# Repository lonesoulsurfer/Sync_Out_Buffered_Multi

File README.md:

Buffered Multiple for Modular Synths - Powered by Arduino

Vid of the Sync in action
https://youtu.be/81T7WBMwU_8

Step by step guide (Instructables)
https://www.instructables.com/Buffered-Multiple-for-Modular-Synths-Powered-by-Ar/

Takes one sync input signal and produces six individually configurable outputs
 - Shows current BPM on OLED display
 - Each output can be configured with:
      - Normal sync (1:1)
      - Clock division (1/2, 1/4, 1/8)
      - Three groove patterns:
          - GS: Swing (delays off-beats by fixed amount)
          - GF: Shuffle (creates triplet-based rhythm)
          - GH: Humanize (adds random timing variations)

Groove Implementation 

Swing (GS) = consistent delayed off-beats
 -Delays off-beats by shifting timing up to 66% through beat
- Very classic swing feel at 50-75% intensities
- Clean implementation with consistent timing

Shuffle (GF) = polyrhythmic feel with specific timing ratios
- Creates 2-against-3 feel using weighted offset timing
- Distinct from swing - pushes toward triplet territory
- At 75%, approaches dotted 8th feeling (funkier)

Humanize (GH) = unpredictable variations
- Adds random timing variation around off-beats
- Much stronger randomization (up to 40% of beat)
- More chaotic/organic feel compared to others

The implementation provides good sonic variety between the modes. Each mode serves a distinct musical purpose, and the intensity levels (50%/75%) allow meaningful adjustment.
The two intensity levels (50% and 75%) offer enough adjustability without overcomplicating the interface. This gives users six distinct groove feels to choose from (three types × two intensities), which is a good balance for this type of device.

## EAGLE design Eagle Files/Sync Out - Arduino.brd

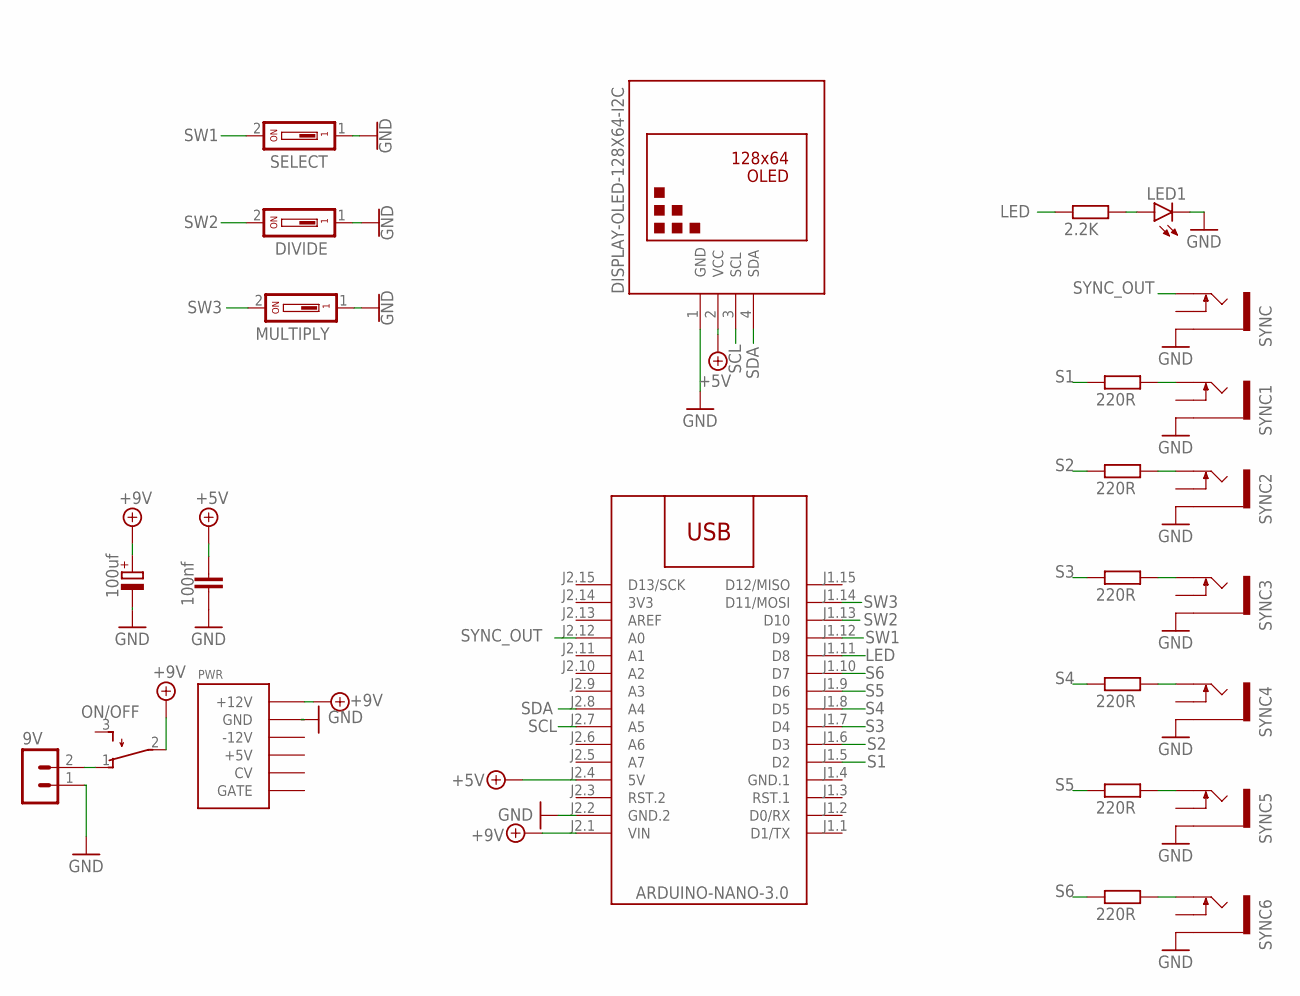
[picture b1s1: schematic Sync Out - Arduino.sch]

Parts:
9V: B2B-PH-K-S
C1: 100nf; C050-024X044
C3: 100uf; E2-5
DIVIDE: DS01; DS-01
LED1: LED3MM
M1: ARDUINO-NANO-3.0
MULTIPLY: DS01; DS-01
ON/OFF: TL32PO; TL3XPO
PWR: POWER; POWER_16
R1, R2, R3, R4, R5, R6: 220R; 0207/10
R7: 2.2K; 0207/10
SELECT: DS01; DS-01
SYNC, SYNC1, SYNC2, SYNC3, SYNC4, SYNC5, SYNC6: THONKICONNNEW; WQP-PJ301M-12_JACK
U$2: DISPLAY-OLED-128X64-I2C

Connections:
3V3: M1.J2.14 (3V3)
+5V: C1.1, M1.J2.4 (5V), U$2.2 (VCC)
+9V: C3.+, M1.J2.1 (VIN), ON/OFF.2, PWR.9 (+12V), PWR.10 (+12V)
GND: 9V.1, C1.2, C3.-, DIVIDE.1, LED1.K (C), M1.J2.2 (GND.2), MULTIPLY.1, PWR.3 (GND), PWR.4 (GND), PWR.5 (GND), PWR.6 (GND), PWR.7 (GND), PWR.8 (GND), SELECT.1, SYNC.P$3_SLEEVE (SLEEVE), SYNC1.P$3_SLEEVE (SLEEVE), SYNC2.P$3_SLEEVE (SLEEVE), SYNC3.P$3_SLEEVE (SLEEVE), SYNC4.P$3_SLEEVE (SLEEVE), SYNC5.P$3_SLEEVE (SLEEVE), SYNC6.P$3_SLEEVE (SLEEVE), U$2.1 (GND)
GND.1: M1.J1.4 (GND.1)
LED: M1.J1.11 (D8), R7.1
unnamed: LED1.A, R7.2
unnamed: 9V.2, ON/OFF.1 (O)
unnamed: R1.2, SYNC1.P$1_TIP (TIP)
unnamed: R2.2, SYNC2.P$1_TIP (TIP)
unnamed: R3.2, SYNC3.P$1_TIP (TIP)
unnamed: R4.2, SYNC4.P$1_TIP (TIP)
unnamed: R5.2, SYNC5.P$1_TIP (TIP)
unnamed: R6.2, SYNC6.P$1_TIP (TIP)
S1: M1.J1.5 (D2), R1.1
S2: M1.J1.6 (D3), R2.1
S3: M1.J1.7 (D4), R3.1
S4: M1.J1.8 (D5), R4.1
S5: M1.J1.9 (D6), R5.1
S6: M1.J1.10 (D7), R6.1
SCL: M1.J2.7 (A5), U$2.3 (SCL)
SDA: M1.J2.8 (A4), U$2.4 (SDA)
SW1: M1.J1.12 (D9), SELECT.2
SW2: DIVIDE.2, M1.J1.13 (D10)
SW3: M1.J1.14 (D11/MOSI), MULTIPLY.2
SYNC_OUT: M1.J2.12 (A0), SYNC.P$1_TIP (TIP)

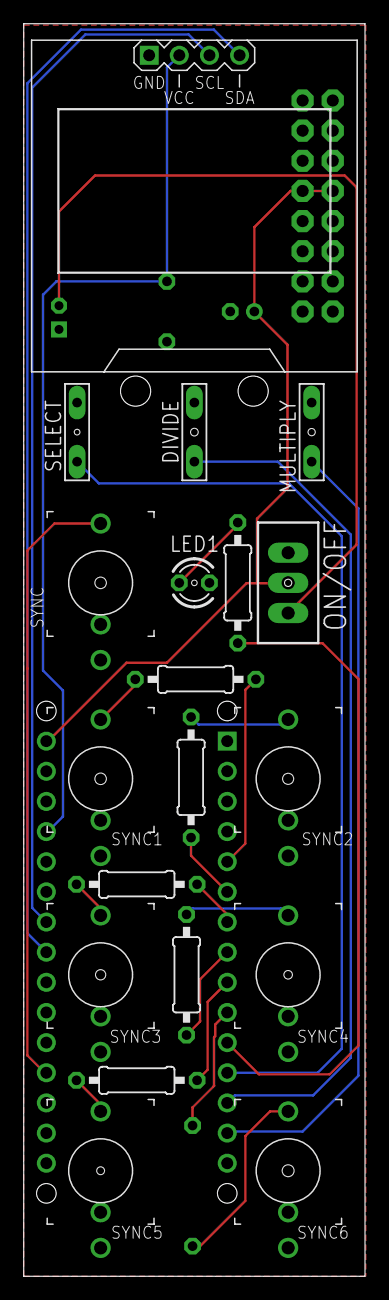
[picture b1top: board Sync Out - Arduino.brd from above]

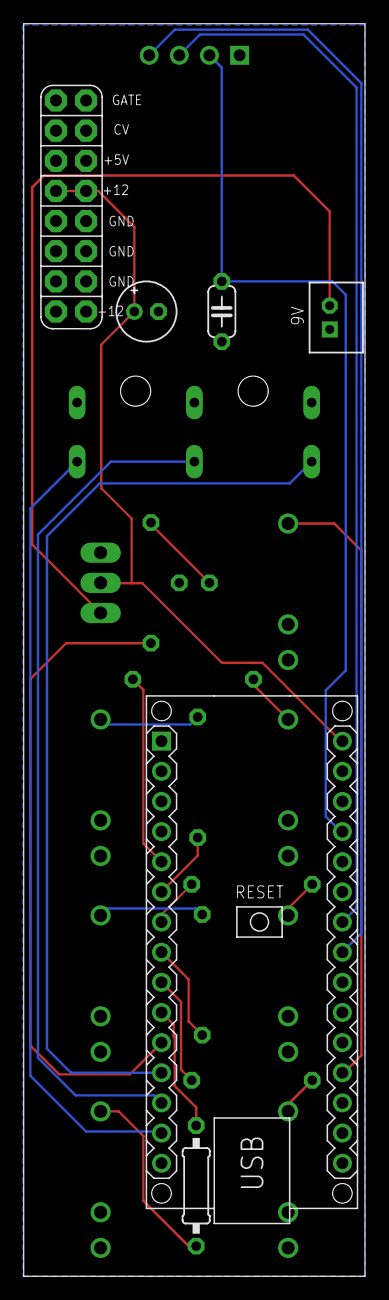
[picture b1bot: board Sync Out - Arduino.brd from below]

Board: 2 copper layers, 28.8 x 105.5 mm, 25 parts (6 on the bottom side), 24 nets.

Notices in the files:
parts and their libraries:
diy-modules: Released under the Creative Commons Attribution 4.0 International License: http://creativecommons.org/licenses/by/4.0
SparkFun-PowerSymbols: Licensing: Creative Commons ShareAlike 4.0 International - https://creativecommons.org/licenses/by-sa/4.0
